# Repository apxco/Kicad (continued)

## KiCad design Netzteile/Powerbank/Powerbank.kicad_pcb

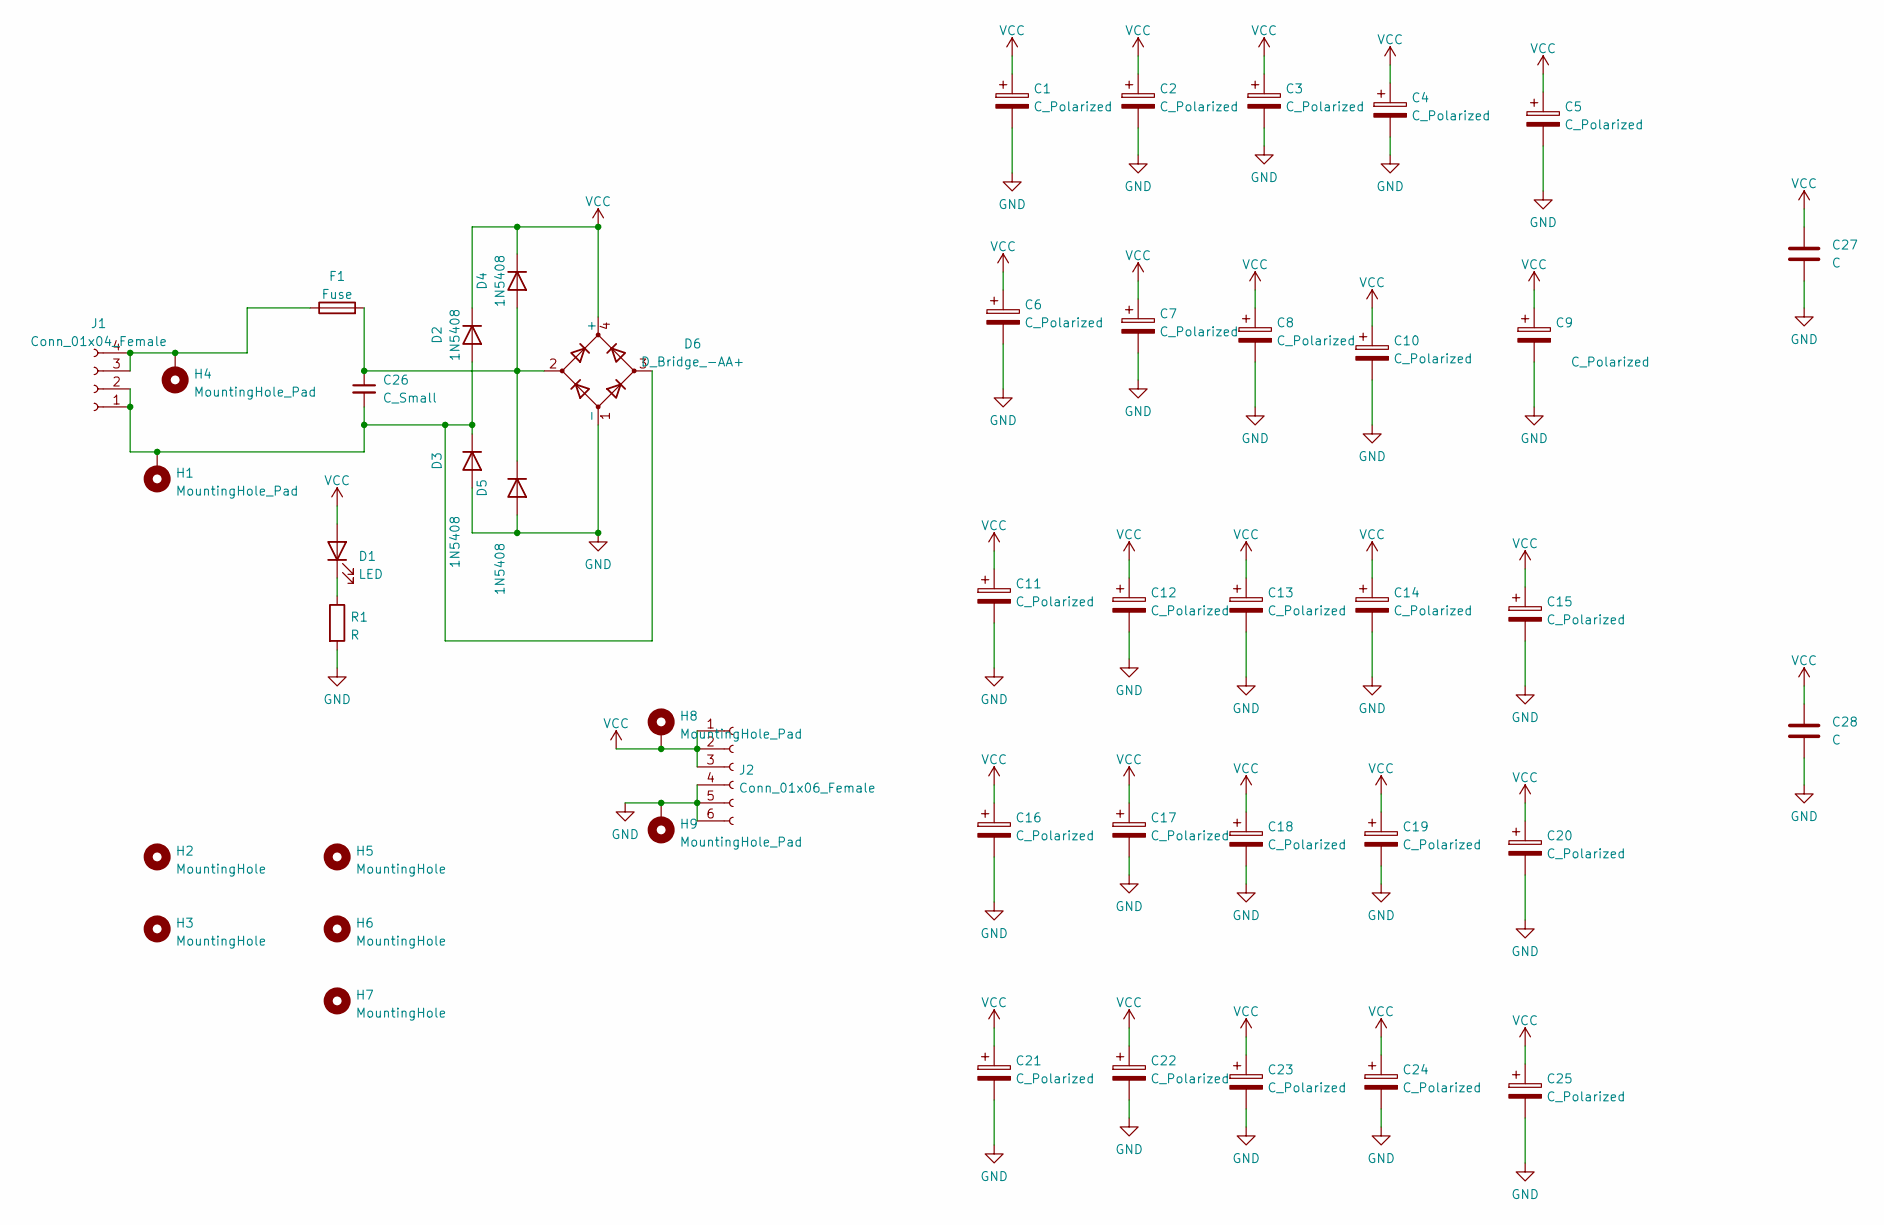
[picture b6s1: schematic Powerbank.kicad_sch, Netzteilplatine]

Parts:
C1, C2, C3, C4, C5, C6, C7, C8, C9, C10, C11, C12, C13, C14, C15, C16, C17, C18, C19, C20, C21, C22, C23, C24, C25: C_Polarized; CP_Radial_D10.0mm_P5.00mm_P7.50mm
C26: C_Small; C_Axial_L12.0mm_D6.5mm_P15.00mm_Horizontal
C27, C28: C; C_Rect_L16.5mm_W5.0mm_P15.00mm_MKT
D1: LED; LED_D3.0mm_Clear
D2, D3, D4, D5: 1N5408; D_DO-201AD_P15.24mm_Horizontal
D6: D_Bridge_-AA+; Diode_Bridge_Vishay_GBU
F1: Fuse; Fuseholder_Littelfuse_100_series_5x20mm
H1, H4, H8, H9: MountingHole_Pad; MountingHole_3.2mm_M3_Pad_TopBottom
H2, H3, H5, H6, H7: MountingHole; MountingHole_3.5mm_Pad
J1: Conn_01x04_Female; TerminalBlock_RND_205-00278_1x04_P5.00mm_Vertical
J2: Conn_01x06_Female; TerminalBlock_RND_205-00060_1x06_P5.00mm_45Degree
R1: R; R_Axial_DIN0204_L3.6mm_D1.6mm_P7.62mm_Horizontal

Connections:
GND: C1.2, C2.2, C3.2, C4.2, C5.2, C6.2, C7.2, C8.2, C9.2, C10.2, C11.2, C12.2, C13.2, C14.2, C15.2, C16.2, C17.2, C18.2, C19.2, C20.2, C21.2, C22.2, C23.2, C24.2, C25.2, C27.2, C28.2, D3.2 (A), D5.2 (A), D6.1 (-), H9.1, J2.4, J2.5, J2.6, R1.2
unnamed: D1.1 (K), R1.1
unnamed: C26.2, D2.2 (A), D3.1 (K), D6.3, H1.1, J1.1, J1.2
unnamed: C26.1, D4.2 (A), D5.1 (K), D6.2, F1.2
unnamed: F1.1, H4.1, J1.3, J1.4
VCC: C1.1, C2.1, C3.1, C4.1, C5.1, C6.1, C7.1, C8.1, C9.1, C10.1, C11.1, C12.1, C13.1, C14.1, C15.1, C16.1, C17.1, C18.1, C19.1, C20.1, C21.1, C22.1, C23.1, C24.1, C25.1, C27.1, C28.1, D1.2 (A), D2.1 (K), D4.1 (K), D6.4 (+), H8.1, J2.1, J2.2, J2.3

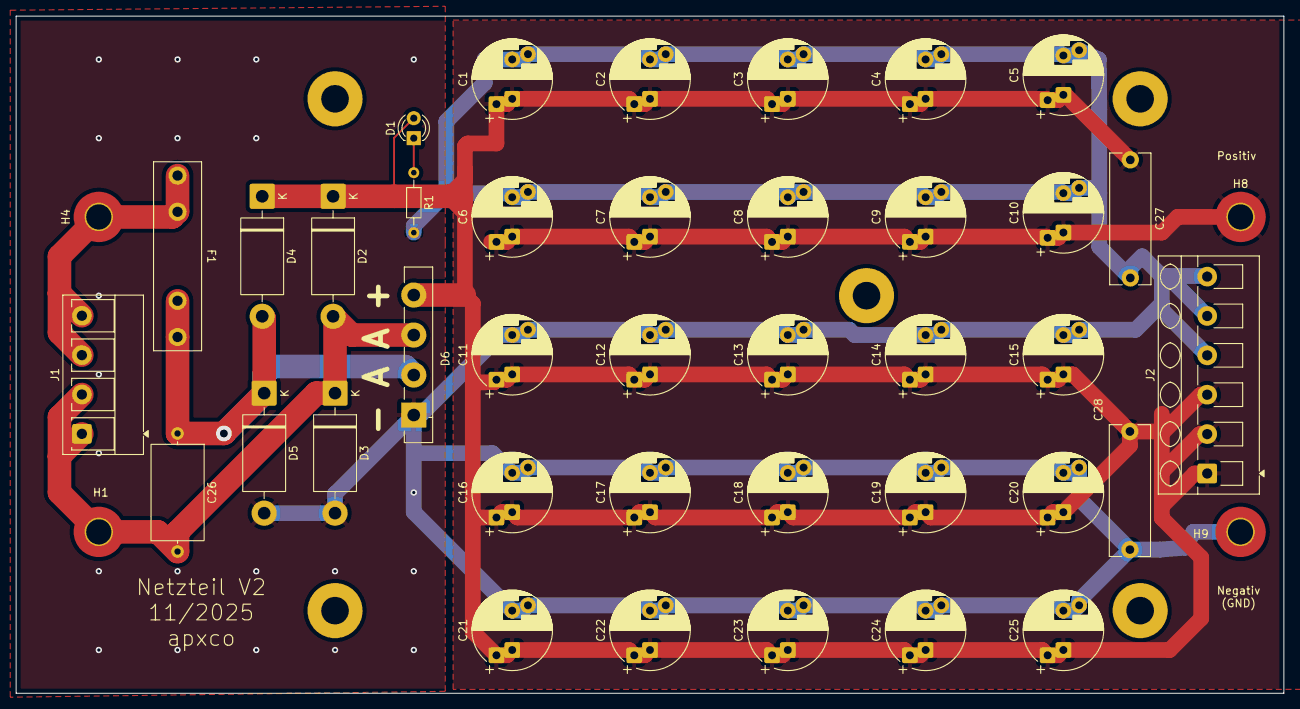
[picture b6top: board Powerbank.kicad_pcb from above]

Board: 2 copper layers, 161.0 x 86.0 mm, 47 parts (0 on the bottom side), 6 nets.

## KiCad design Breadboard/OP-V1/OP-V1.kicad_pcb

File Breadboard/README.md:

Kleine Helfer für das Steckbrett

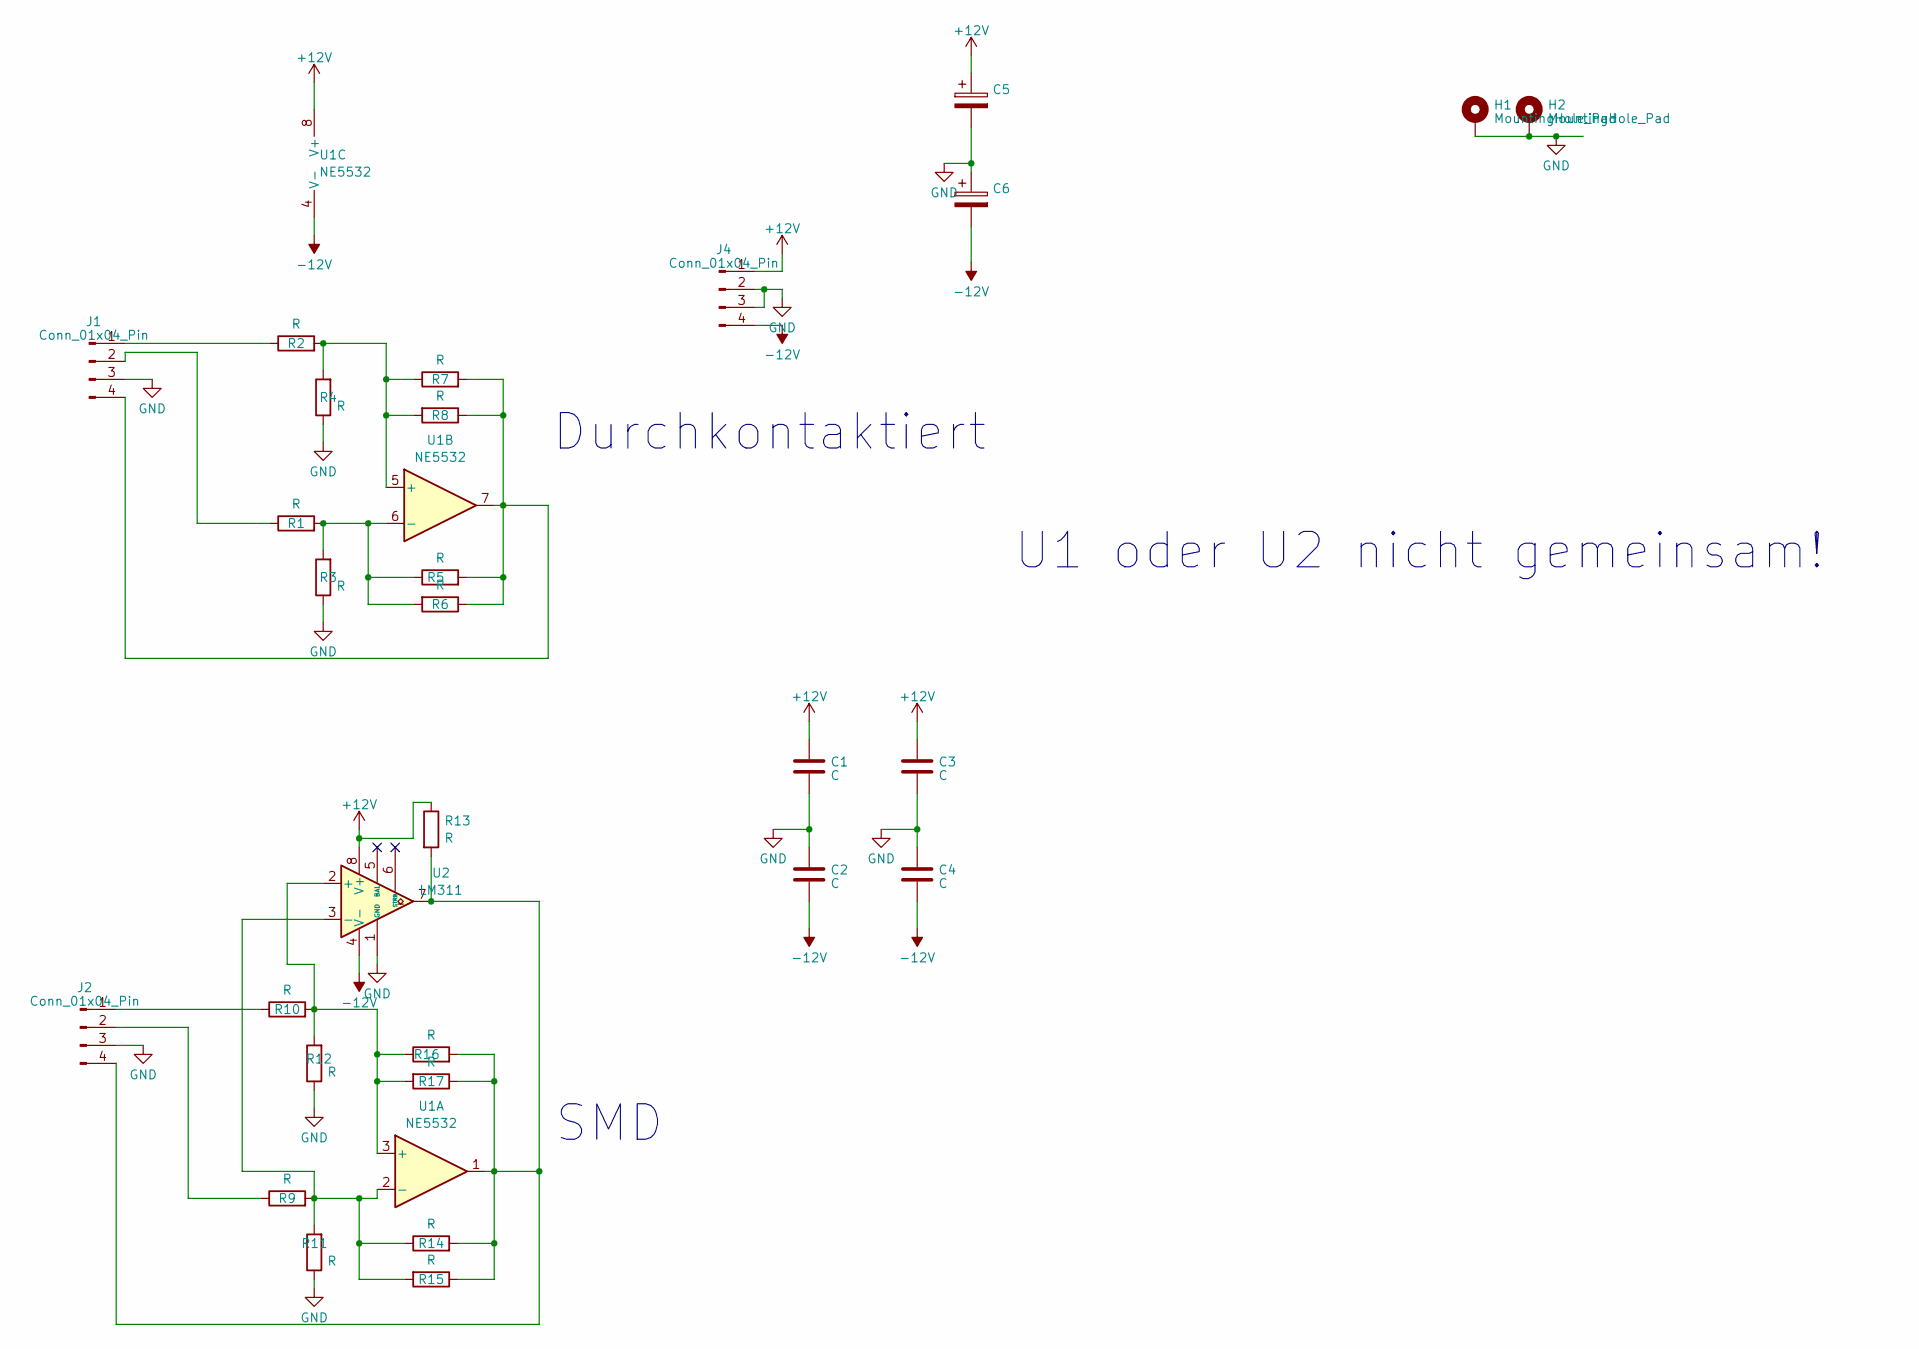
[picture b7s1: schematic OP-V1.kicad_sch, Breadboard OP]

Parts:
C1, C2, C3, C4: C; C_0805_2012Metric_Pad1.18x1.45mm_HandSolder
C5, C6: C_Polarized; CP_Elec_6.3x5.9
H1, H2: MountingHole_Pad; MountingHole_3.2mm_M3_DIN965_Pad_TopBottom
J1, J2: Conn_01x04_Pin; PinHeader_1x04_P2.54mm_Vertical
J4: Conn_01x04_Pin; PinSocket_1x04_P2.54mm_Vertical
R1, R2, R3, R4, R5, R6, R7, R8: R; R_Axial_DIN0204_L3.6mm_D1.6mm_P7.62mm_Horizontal
R9, R10, R11, R12, R13, R14, R15, R16, R17: R; R_0805_2012Metric_Pad1.20x1.40mm_HandSolder
U1: NE5532; SOIC-8_3.9x4.9mm_P1.27mm
U2: LM311; SOIC-8_3.9x4.9mm_P1.27mm

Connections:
+12V: C1.1, C3.1, C5.1, J4.1, R13.1, U1.8 (V+), U2.8 (V+)
-12V: C2.2, C4.2, C6.2, J4.4, U1.4 (V-), U2.4 (V-)
GND: C1.2, C2.1, C3.2, C4.1, C5.2, C6.1, H1.1, H2.1, J1.3, J2.3, J4.2, J4.3, R3.1, R4.1, R11.1, R12.1, U2.1 (GND)
unnamed: J1.1, R2.1
unnamed: J1.2, R1.1
unnamed: J1.4, R5.2, R6.1, R7.2, R8.1, U1.7
unnamed: J2.1, R10.1
unnamed: J2.2, R9.1
unnamed: J2.4, R13.2, R14.2, R15.1, R16.2, R17.1, U1.1, U2.7
unnamed: R10.2, R12.2, R16.1, R17.2, U1.3 (+), U2.2 (+)
unnamed: R9.2, R11.2, R14.1, R15.2, U1.2 (-), U2.3 (-)
unnamed: R2.2, R4.2, R7.1, R8.2, U1.5 (+)
unnamed: R1.2, R3.2, R5.1, R6.2, U1.6 (-)

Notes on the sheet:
U1 oder U2 nicht gemeinsam!
Durchkontaktiert
SMD

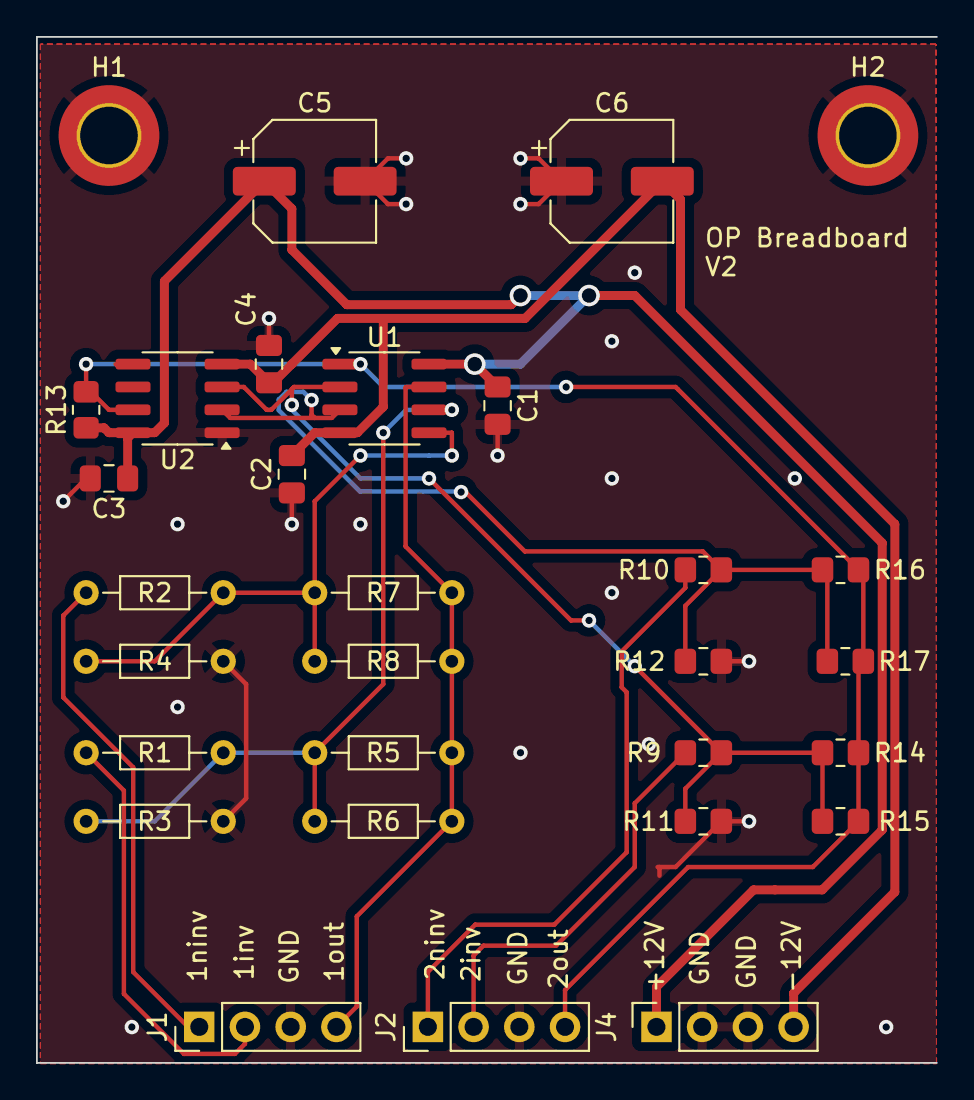
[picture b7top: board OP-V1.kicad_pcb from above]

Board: 2 copper layers, 50.0 x 57.0 mm, 30 parts (0 on the bottom side), 13 nets.

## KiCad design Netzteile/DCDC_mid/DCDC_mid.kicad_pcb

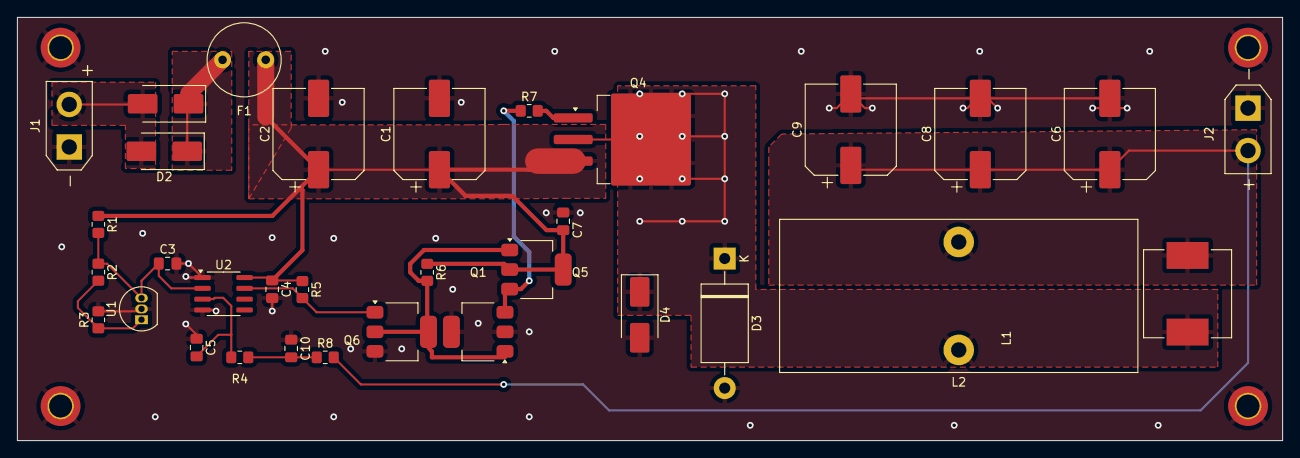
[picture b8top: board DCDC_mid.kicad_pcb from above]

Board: 2 copper layers, 148.8 x 49.8 mm, 37 parts (0 on the bottom side), 14 nets.

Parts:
C1, C2, C6, C8, C9: C_Polarized; CP_Elec_10x12.5
C3, C4, C5, C7, C10: 100n; C_0805_2012Metric_Pad1.18x1.45mm_HandSolder
D1, D2, D4: D; D_SMB_Handsoldering
D3: D; D_DO-201AE_P15.24mm_Horizontal
F1: Fuse; Fuse_Littelfuse_372_D8.50mm
H1, H2, H3, H4: MountingHole_Pad; MountingHole_2.7mm_M2.5_DIN965_Pad_TopOnly
J1, J2: Conn_01x02_Pin; AMASS_XT30UPB-M_1x02_P5.0mm_Vertical
L1: L; L_Vishay_IHLP-4040
L2: L; L_Toroid_Vertical_L41.9mm_W17.8mm_P12.70mm_Pulse_F
Q1: FTZ953; SOT-223-3_TabPin2
Q4: Q_PMOS_GDSD; TO-263-3_TabPin4
Q5, Q6: FTZ853; SOT-223-3_TabPin2
R1: 680; R_0805_2012Metric_Pad1.20x1.40mm_HandSolder
R2, R4, R8: 13k; R_0805_2012Metric_Pad1.20x1.40mm_HandSolder
R3, R5: 3k; R_0805_2012Metric_Pad1.20x1.40mm_HandSolder
R6: 470; R_0805_2012Metric_Pad1.20x1.40mm_HandSolder
R7: 1R; R_0805_2012Metric_Pad1.20x1.40mm_HandSolder
U1: TL431LP; TO-92_Inline
U2: LM311; SOIC-8_3.9x4.9mm_P1.27mm

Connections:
+VDC: C1.1, C2.1, C4.1, C7.2, F1.2, Q4.3 (S), Q5.2 (C), R1.1, R5.1, R6.1, U2.8 (V+)
GND: C1.2, C2.2, C3.2, C4.2, C5.1, C6.2, C7.1, C8.2, C9.2, C10.1, D3.2 (A), D4.2 (A), H1.1, H2.1, H3.1, H4.1, J1.1, J2.1, Q1.2 (C), Q6.3 (E), R3.2, U1.2 (A), U2.1 (GND), U2.4 (V-)
unnamed: C10.2, R4.2, R8.1
unnamed: D1.2 (A), D2.2 (A), J1.2
unnamed: D1.1 (K), D2.1 (K), F1.1
unnamed: D3.1 (K), D4.1 (K), L1.1, L2.1, Q4.2 (D), Q4.4 (D)
unnamed: C6.1, C8.1, C9.1, J2.2, L1.2, L2.2, R8.2
unnamed: Q1.1 (B), Q5.1 (B), Q6.2 (C), R6.2
unnamed: Q1.3 (E), Q5.3 (E), R7.1
unnamed: Q4.1 (G), R7.2
unnamed: Q6.1 (B), R5.2, U2.7
unnamed: C3.1, R1.2, R2.1, U1.3 (K), U2.2 (+)
unnamed: R2.2, R3.1, U1.1 (REF)
unnamed: C5.2, R4.1, U2.3 (-)

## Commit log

2024-08-10 Add files via upload
    In dieser Version wurde die Platine noch nicht nachgebaut von mir.
2024-08-10 Add files via upload
    So noch nicht getestet von mir.
2024-08-10 Add files via upload
    In der Version noch nicht getestet, glaube ich.
2024-08-10 Add files via upload
    Wurde aufgebaut, funktioniert soweit.
2024-08-10 Add files via upload
    Vorgängerverson gebaut, verschiedene Verbesserungen in dieser Version. Nicht getestet.
2024-08-15 Anschlussleiste auf 2,56 mm Rastermaß geändert.
2024-08-17 DCDC_mit verbessert, hoffentlich
2024-08-19 DCDC_mid überarbeitet
2024-08-23 DCDCmid Andere Transistoren
2024-08-31 Powerstage2 bearbeitet
2024-09-01 Version 2 für Herstellung
2024-09-01 V4 für Produktion
2024-10-01 Kleinere Änderungen
2024-11-23 Powerstage2 und HBrücke3 Aufgebaut und verbesserungen eingearbeitet.
2025-02-03 Finalisierung Netzteilplatine
2025-06-08 Verschiedene Anpassungen in 2 Projekten. Netzteil Aufgebaut und OK. D-Amp funktioniert aber totes Ende im Projekt erreicht.
2025-09-05 Anlegen Projekt Useless Relais Addierer
2025-09-08 Version 1.0 Noch nicht getestet, keine Platine hergestellt.
2025-09-08 Ordner Backubs entfernt
2025-09-08 RelaisAddierer Platine erstellt, Screenshot zugefügt
2025-09-08 Bild hinzugefügt
2025-09-08 von txt zu md geändert
2025-09-08 rm bearbeitet
2025-09-10 Aufräumarbeiten Projektbeschreibung
2025-09-10 Aufräumarbeiten
2025-09-12 Namensänderung Software hinzugefügt
2025-09-13 Steckbretter Schaltungen neu geordnet
2025-09-13 Relaisrechner Programmierung begonnen
2025-10-24 Useless Adder auf V2.0 gebracht. Software finalisiert, Platine benötigt noch Arbeit
2025-10-24 DRC durchgeführt und Fehler korrigiert, Platine verschönert
2025-10-24 Bild von Rückseite und YouTube Link
2025-10-24 neuer Versuch
2025-11-01 Powerbank überarbeitet, Powerbank mit dual Ausgnagsspannung angelegt
2025-11-01 Useless Relais Adder Software ergänzt
2025-11-01 BOM ergänzt
2025-11-01 Umsortiert
2025-11-02 Netzteile überarbeitet, neu sortiert
2025-12-06 Bilder ergänzt
2025-12-06 Relais AdderII Ordner und readme angelegt,
2025-12-06 solder mask to copper clearance geändert
2025-12-12 Schieberegister und Treiber Carry bearbeitet
2026-01-04 Spannungsteiler statt Widerstand für Eingangsstufe
2026-02-04 Useless Relais Adder II hinzugefügt
2026-02-05 Powerbank II Pads an Bauteil angepasst
2026-02-07 Erste Testversion der Platine abgeschlossen
2026-02-07 Rechtschreibfehler korrigiert
2026-02-07 Kleine Text Bearbeitung
2026-03-15 Version 1.0 für Platinenherstellung
